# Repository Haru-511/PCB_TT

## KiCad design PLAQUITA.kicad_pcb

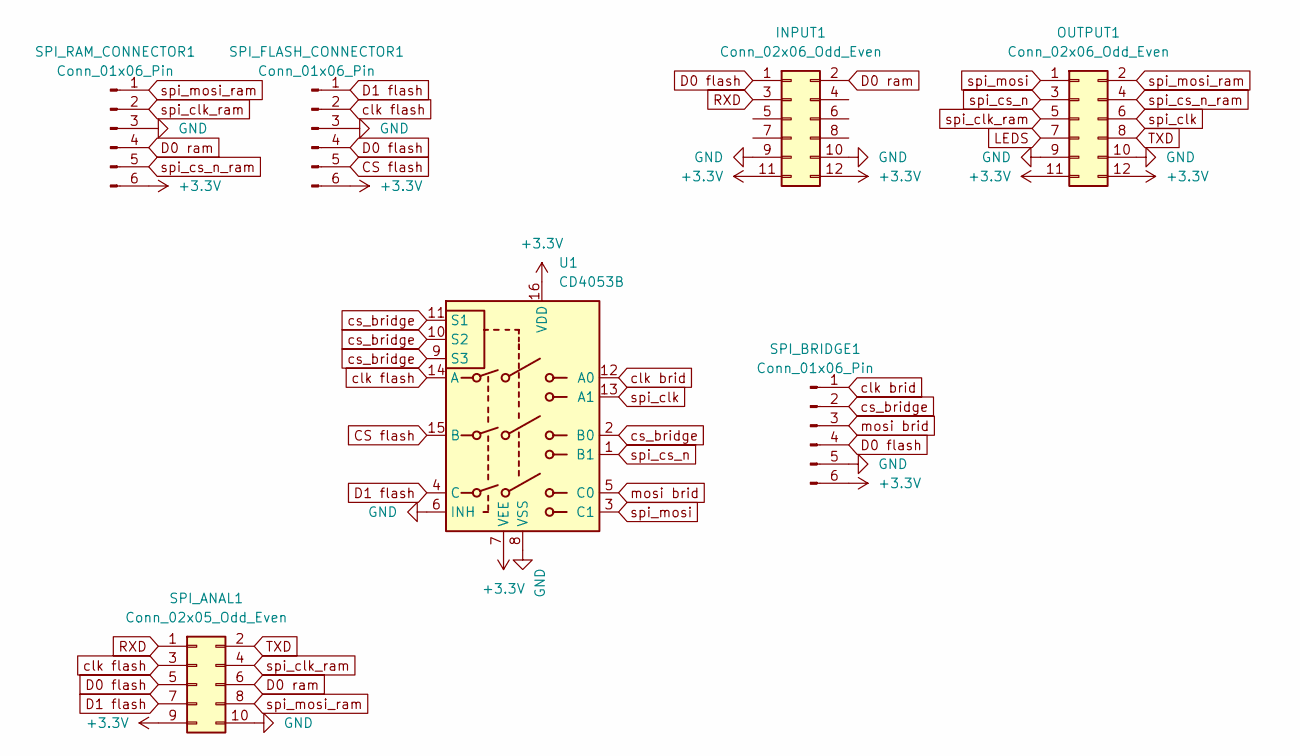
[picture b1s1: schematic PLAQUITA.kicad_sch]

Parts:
INPUT1: Conn_02x06_Odd_Even; PinHeader_2x06_P2.54mm_Horizontal
OUTPUT1: Conn_02x06_Odd_Even; PinHeader_2x06_P2.54mm_Horizontal
SPI_ANAL1: Conn_02x05_Odd_Even; IDC-Header_2x05_P2.54mm_Horizontal
SPI_BRIDGE1: Conn_01x06_Pin; PinHeader_1x06_P2.54mm_Vertical
SPI_FLASH_CONNECTOR1: Conn_01x06_Pin; PinSocket_1x06_P2.54mm_Vertical
SPI_RAM_CONNECTOR1: Conn_01x06_Pin; PinSocket_1x06_P2.54mm_Vertical
U1: CD4053B; DIP-16_W7.62mm_LongPads

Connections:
+3.3V: INPUT1.11, INPUT1.12, OUTPUT1.11, OUTPUT1.12, SPI_ANAL1.9, SPI_BRIDGE1.6, SPI_FLASH_CONNECTOR1.6, SPI_RAM_CONNECTOR1.6, U1.7 (VEE), U1.16 (VDD)
CS flash: SPI_FLASH_CONNECTOR1.5, U1.15 (B)
D0 flash: INPUT1.1, SPI_ANAL1.5, SPI_BRIDGE1.4, SPI_FLASH_CONNECTOR1.4
D0 ram: INPUT1.2, SPI_ANAL1.6, SPI_RAM_CONNECTOR1.4
D1 flash: SPI_ANAL1.7, SPI_FLASH_CONNECTOR1.1, U1.4 (C)
GND: INPUT1.9, INPUT1.10, OUTPUT1.9, OUTPUT1.10, SPI_ANAL1.10, SPI_BRIDGE1.5, SPI_FLASH_CONNECTOR1.3, SPI_RAM_CONNECTOR1.3, U1.6 (INH), U1.8 (VSS)
LEDS: OUTPUT1.7
RXD: INPUT1.3, SPI_ANAL1.1
TXD: OUTPUT1.8, SPI_ANAL1.2
clk brid: SPI_BRIDGE1.1, U1.12 (A0)
clk flash: SPI_ANAL1.3, SPI_FLASH_CONNECTOR1.2, U1.14 (A)
cs_bridge: SPI_BRIDGE1.2, U1.2 (B0), U1.9 (S3), U1.10 (S2), U1.11 (S1)
mosi brid: SPI_BRIDGE1.3, U1.5 (C0)
spi_clk: OUTPUT1.6, U1.13 (A1)
spi_clk_ram: OUTPUT1.5, SPI_ANAL1.4, SPI_RAM_CONNECTOR1.2
spi_cs_n: OUTPUT1.3, U1.1 (B1)
spi_cs_n_ram: OUTPUT1.4, SPI_RAM_CONNECTOR1.5
spi_mosi: OUTPUT1.1, U1.3 (C1)
spi_mosi_ram: OUTPUT1.2, SPI_ANAL1.8, SPI_RAM_CONNECTOR1.1

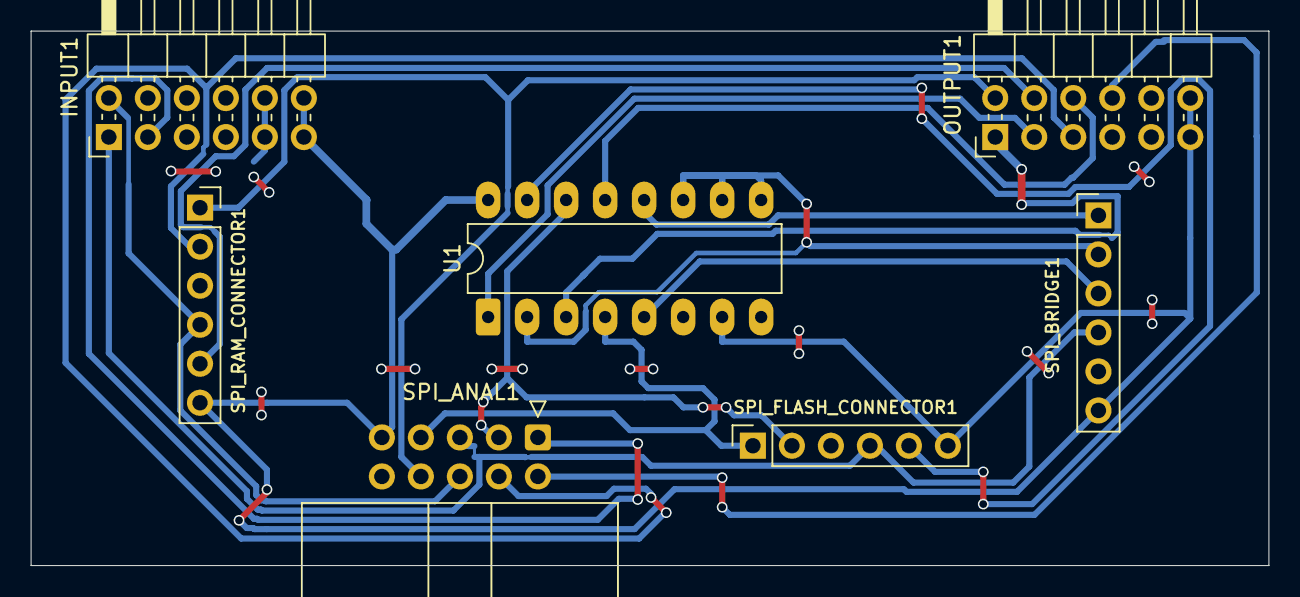
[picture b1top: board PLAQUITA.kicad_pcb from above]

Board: 2 copper layers, 80.6 x 34.8 mm, 7 parts (0 on the bottom side), 18 nets.

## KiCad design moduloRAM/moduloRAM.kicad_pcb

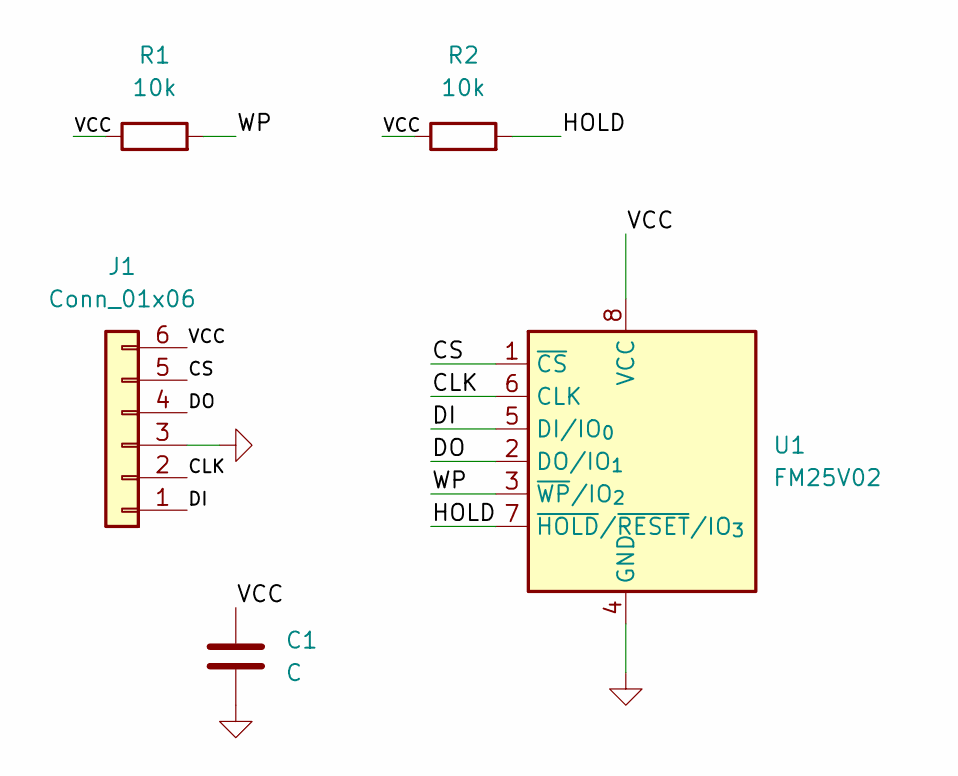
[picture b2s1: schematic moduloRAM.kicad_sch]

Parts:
C1: C; C_0805_2012Metric_Pad1.18x1.45mm_HandSolder
J1: Conn_01x06; PinHeader_1x06_P2.54mm_Vertical
R1, R2: 10k; C_0805_2012Metric_Pad1.18x1.45mm_HandSolder
U1: FM25V02; SOIC-8_5.3x5.3mm_P1.27mm

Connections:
/CLK: J1.2, U1.6 (CLK)
/CS: J1.5, U1.1 (~CS)
/DI: J1.1, U1.5 (DI/IO_{0})
/DO: J1.4, U1.2 (DO/IO_{1})
/HOLD: R2.2, U1.7 (~HOLD/~RESET/IO_{3})
/VCC: C1.1, J1.6, R1.1, R2.1, U1.8 (VCC)
/WP: R1.2, U1.3 (~WP/IO_{2})
GND: C1.2, J1.3, U1.4 (GND)

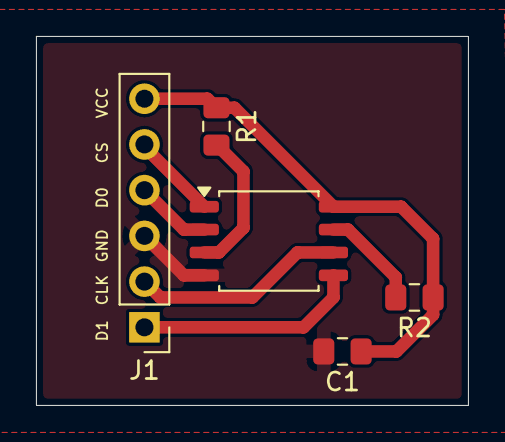
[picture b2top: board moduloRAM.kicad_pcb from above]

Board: 2 copper layers, 24.0 x 20.5 mm, 5 parts (0 on the bottom side), 8 nets.
